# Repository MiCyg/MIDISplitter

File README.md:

# MIDI Splitter

This repository contains the PCB design and enclosure model for a MIDI splitter. The detailed project description and assembly instructions can be found [here](https://www.instructables.com/Another-MIDI-Splitter/).

## Repository Contents

- Files for the printed circuit board (PCB) design with KiCad
- 3D model files for the MIDI splitter's enclosure

## Contributing

Contributions are welcome! Please open an issue or submit a pull request for any improvements or bug fixes.

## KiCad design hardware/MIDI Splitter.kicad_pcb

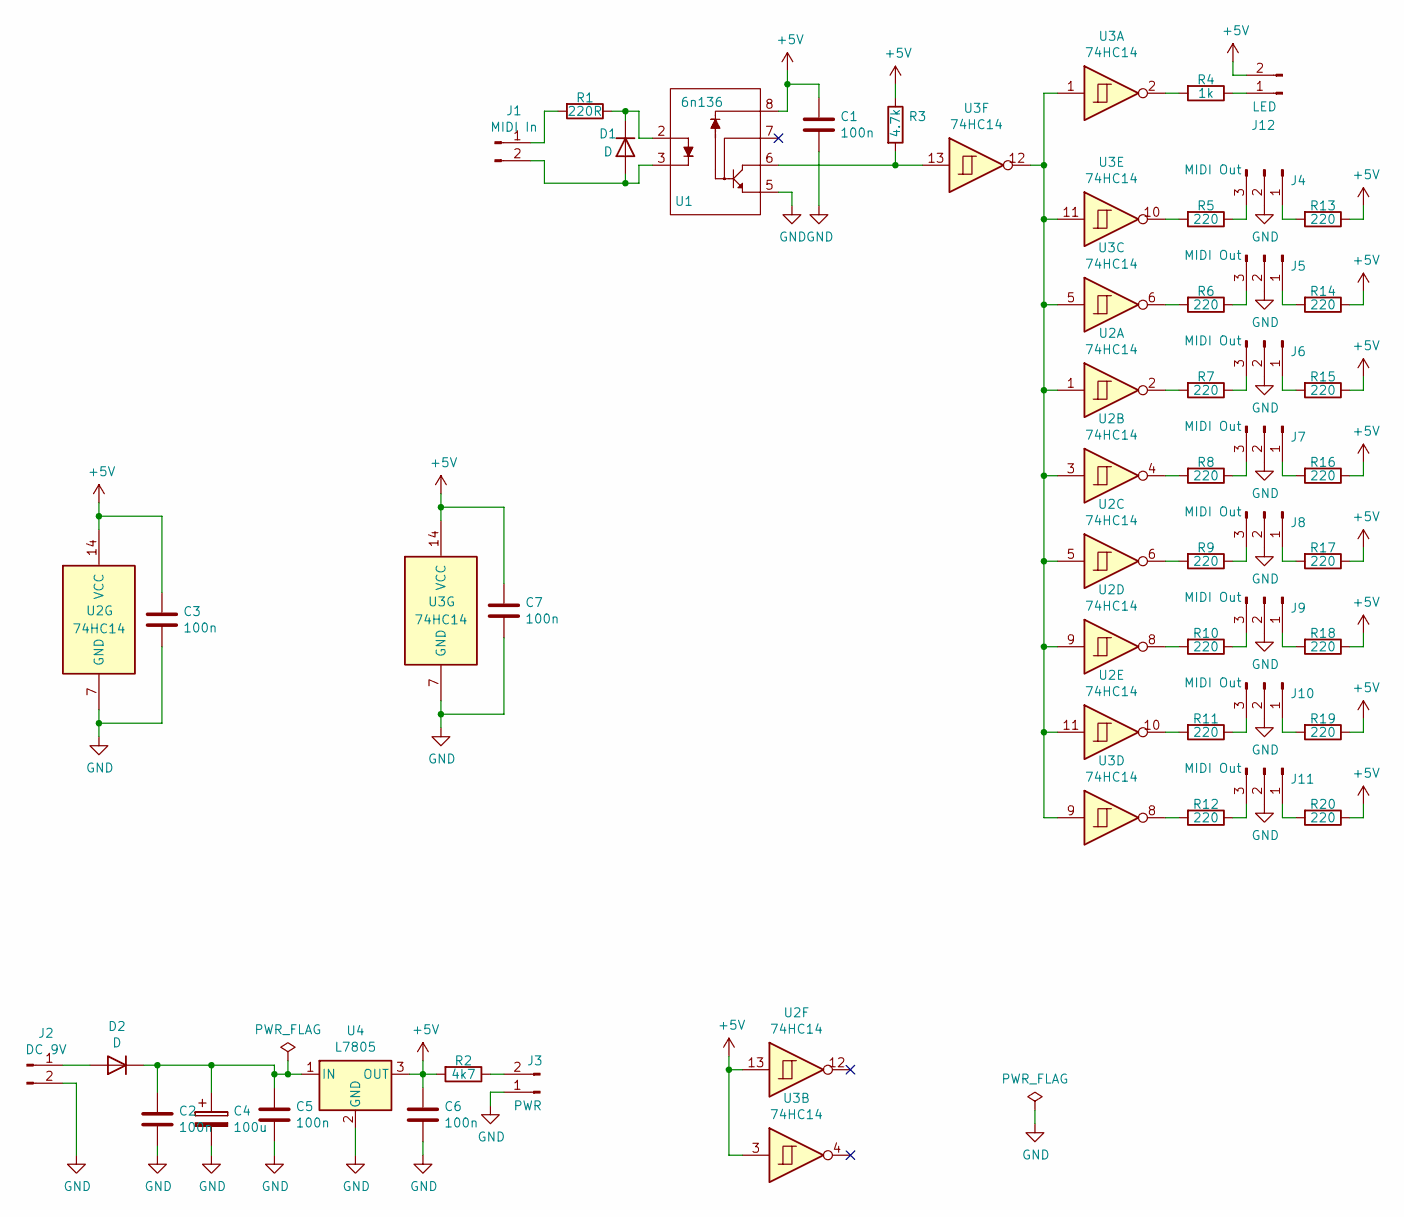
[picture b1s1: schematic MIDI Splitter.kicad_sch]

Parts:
C1, C2, C3, C5, C6, C7: 100n; C_Disc_D5.0mm_W2.5mm_P2.50mm
C4: 100u; CP_Radial_D5.0mm_P2.50mm
D1, D2: D; D_T-1_P5.08mm_Horizontal
J1: MIDI In; Molex_KK-254_AE-6410-02A_1x02_P2.54mm_Vertical
J2: DC 9V; Molex_KK-254_AE-6410-02A_1x02_P2.54mm_Vertical
J3: PWR; Molex_KK-254_AE-6410-02A_1x02_P2.54mm_Vertical
J4, J5, J6, J7, J8, J9, J10, J11: MIDI Out; Molex_KK-254_AE-6410-03A_1x03_P2.54mm_Vertical
J12: LED; Molex_KK-254_AE-6410-02A_1x02_P2.54mm_Vertical
R1: 220R; R_Axial_DIN0207_L6.3mm_D2.5mm_P7.62mm_Horizontal
R2: 4k7; R_Axial_DIN0207_L6.3mm_D2.5mm_P7.62mm_Horizontal
R3: 4.7k; R_Axial_DIN0207_L6.3mm_D2.5mm_P7.62mm_Horizontal
R4: 1k; R_Axial_DIN0207_L6.3mm_D2.5mm_P7.62mm_Horizontal
R5, R6, R7, R8, R9, R10, R11, R12, R13, R14, R15, R16, R17, R18, R19, R20: 220; R_Axial_DIN0207_L6.3mm_D2.5mm_P7.62mm_Horizontal
U1: 6n136; DIP-8_W7.62mm_LongPads
U2, U3: 74HC14; DIP-14_W7.62mm_LongPads
U4: L7805; TO-220-3_Vertical

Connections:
+5V: C1.1, C3.1, C6.1, C7.1, J12.2, R2.2, R3.1, R13.1, R14.1, R15.1, R16.1, R17.1, R18.1, R19.1, R20.1, U1.8, U2.13, U2.14 (VCC), U3.3, U3.14 (VCC), U4.3 (OUT)
GND: C1.2, C2.2, C3.2, C4.2, C5.2, C6.2, C7.2, J2.2, J3.1, J4.2, J5.2, J6.2, J7.2, J8.2, J9.2, J10.2, J11.2, U1.5, U2.7 (GND), U3.7 (GND), U4.2 (GND)
unnamed: D1.2 (A), J1.2, U1.3
unnamed: D1.1 (K), R1.1, U1.2
unnamed: D2.2 (A), J2.1
unnamed: C2.1, C4.1, C5.1, D2.1 (K), U4.1 (IN)
unnamed: J1.1, R1.2
unnamed: J3.2, R2.1
unnamed: J4.1, R13.2
unnamed: J4.3, R5.1
unnamed: J5.1, R14.2
unnamed: J5.3, R6.1
unnamed: J6.1, R15.2
unnamed: J6.3, R7.1
unnamed: J7.1, R16.2
unnamed: J7.3, R8.1
unnamed: J8.1, R17.2
unnamed: J8.3, R9.1
unnamed: J9.1, R18.2
unnamed: J9.3, R10.1
unnamed: J10.1, R19.2
unnamed: J10.3, R11.1
unnamed: J11.1, R20.2
unnamed: J11.3, R12.1
unnamed: J12.1, R4.1
unnamed: R3.2, U1.6, U3.13
unnamed: R4.2, U3.2
unnamed: R5.2, U3.10
unnamed: R6.2, U3.6
unnamed: R7.2, U2.2
unnamed: R8.2, U2.4
unnamed: R9.2, U2.6
unnamed: R10.2, U2.8
unnamed: R11.2, U2.10
unnamed: R12.2, U3.8
unnamed: U2.1, U2.3, U2.5, U2.9, U2.11, U3.1, U3.5, U3.9, U3.11, U3.12

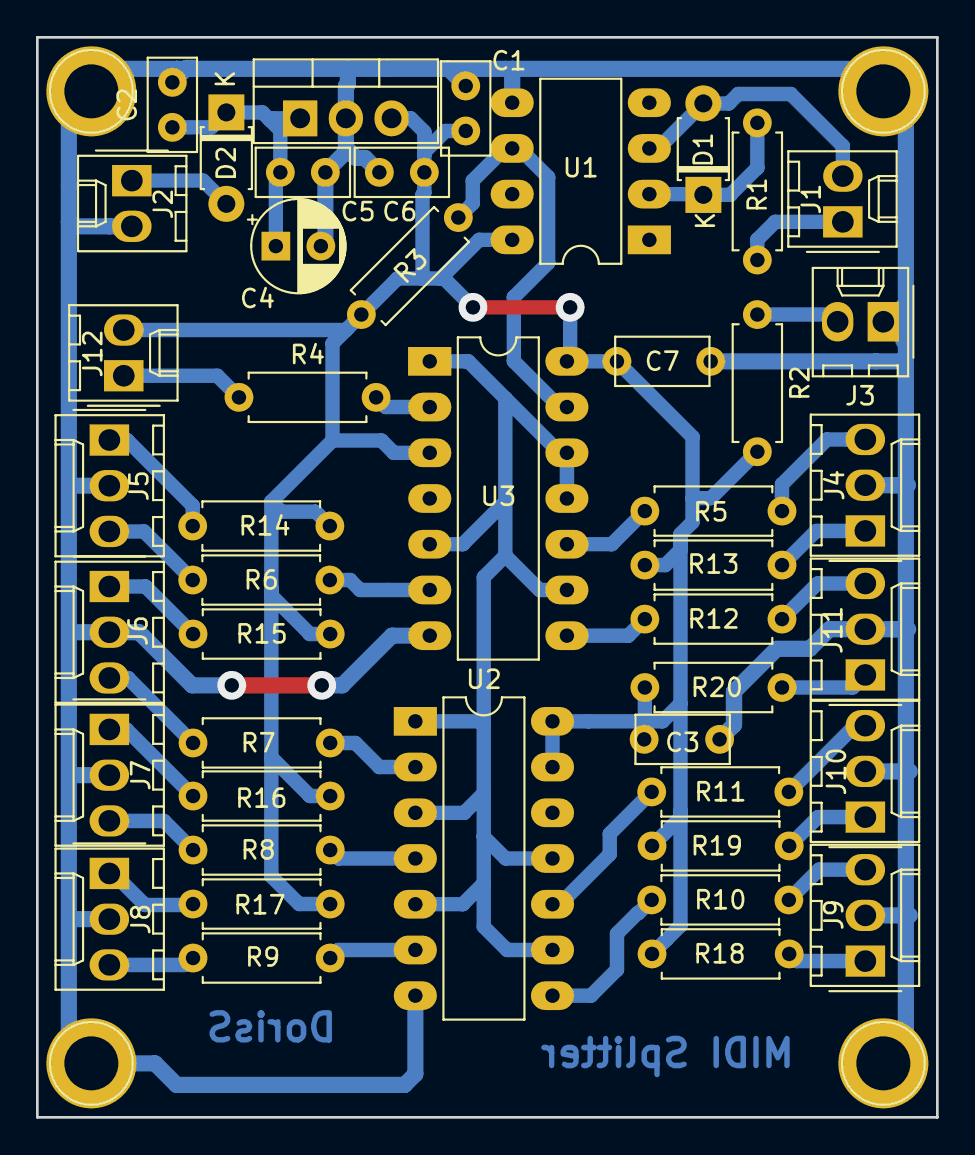
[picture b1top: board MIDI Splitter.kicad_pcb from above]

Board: 2 copper layers, 50.0 x 60.0 mm, 45 parts (0 on the bottom side), 36 nets.

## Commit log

2024-02-14 Initial Commit for project
